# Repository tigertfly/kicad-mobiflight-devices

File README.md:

# KiCAD design blocks for MobiFlight devices

KiCAD [design blocks](https://docs.kicad.org/9.0/en/eeschema/eeschema.html#schematic-design-blocks) are reusable schematic (and PCB) snippets for PCB design. 

## About this repository

This design block library contains blocks for the basic input and output devices supported by [MobiFlight](https://www.mobiflight.com/). It is created with hope that it will be useful for those learning to design printed circuit boards for their flight simulator projects, and to have a reference schematics for the device wiring in the documentation.

This is a work in progress, and at least for now, the design blocks are mostly for schematics, as PCB layouts are more specific to particular panel layouts. 

The footprints use through-hole (THT) components by default, to be more accessible for most simulator builders. If you are more experienced in PCB design, you can of course change them to suit your preferences. For Some blocks there might also be a surface mount version - such blocks will likely contain `SMD` in their name.

### Additional resources
This design block library might reference some component footprints from the [kicad sim panel components -library](https://github.com/MobiFlight/kicad-sim-panel-components), installing it along this one is likely useful.

### Installation

You can download this repository as a `zip` file, but since it is likely in active development at this point, it might be better to use `git` to clone the repository on your computer, and pull updates from git when things are updated. I am sure things will settle later and we'll do a proper release, but for now mind the gaps and watch your head, figuratively speaking.

You can install the library via the KiCAD main window menu: `Preferences → Manage Design Block Libraries`. Choose the folder icon in the small toolbar (`Add existing`)

Navigate to the "kicad-mobiflight-device-blocks" folder, and click `OK` to add the design block library. You likely will need to open the design blocks panel from the KiCAD schematic editor menu `View → Panels → Design Blocks`.

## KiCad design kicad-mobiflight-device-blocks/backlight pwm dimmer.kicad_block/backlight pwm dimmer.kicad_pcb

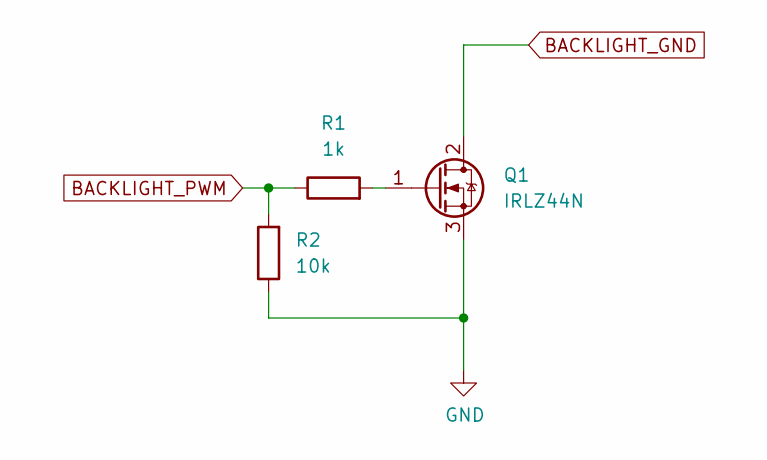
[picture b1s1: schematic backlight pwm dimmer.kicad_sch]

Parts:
Q1: IRLZ44N; TO-220-3_Horizontal_TabDown
R1: 1k; R_Axial_DIN0207_L6.3mm_D2.5mm_P10.16mm_Horizontal; LCSC Part # C21190
R2: 10k; R_Axial_DIN0207_L6.3mm_D2.5mm_P10.16mm_Horizontal; LCSC Part # C25804

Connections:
BACKLIGHT_GND: Q1.2 (D)
BACKLIGHT_PWM: R1.1, R2.2
GND: Q1.3 (S), R2.1
unnamed: Q1.1 (G), R1.2

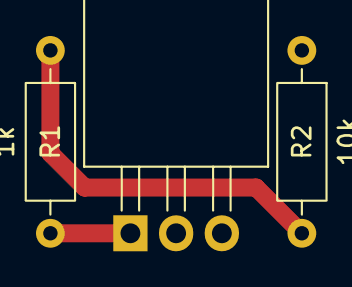
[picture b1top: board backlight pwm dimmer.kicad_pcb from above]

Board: 2 copper layers, 3 parts (0 on the bottom side), 3 nets.

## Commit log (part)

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2026-03-14 edited readme some more
2026-03-28 renamed indicator led block
2026-03-28 added backlight LED, and backlight dimmer circuit schematic blocks
2026-03-28 added .code-workspace to gitignore, they are machine specific paths.
2026-03-28 layout tweaks, added frame and label aroundm, figured device-level blocks could be labeled for clarity.
2026-03-28 renamed for consistency.
2026-03-28 back and forth with naming and whether to use net labels or global, global for now.
2026-03-28 adjusted footprint sizes (THT) and label naming for input shifter.
2026-03-28 resstor footprint (I think!) and the net label for leds
2026-03-28 added daisy chain info
2026-03-28 added design block for output shift register
2026-03-28 added photoresistor (light sensor) design block
2026-03-28 moved the blocks library to a subfolder
2026-03-28 updated README with some work in progress instructions
